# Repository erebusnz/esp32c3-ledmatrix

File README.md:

# esp32c3 Led Matrix 6x8x8
 Led Matrix 6x 60mm 8x8 dot-matrix modules drive by max7221/7219 and an esp32c3.

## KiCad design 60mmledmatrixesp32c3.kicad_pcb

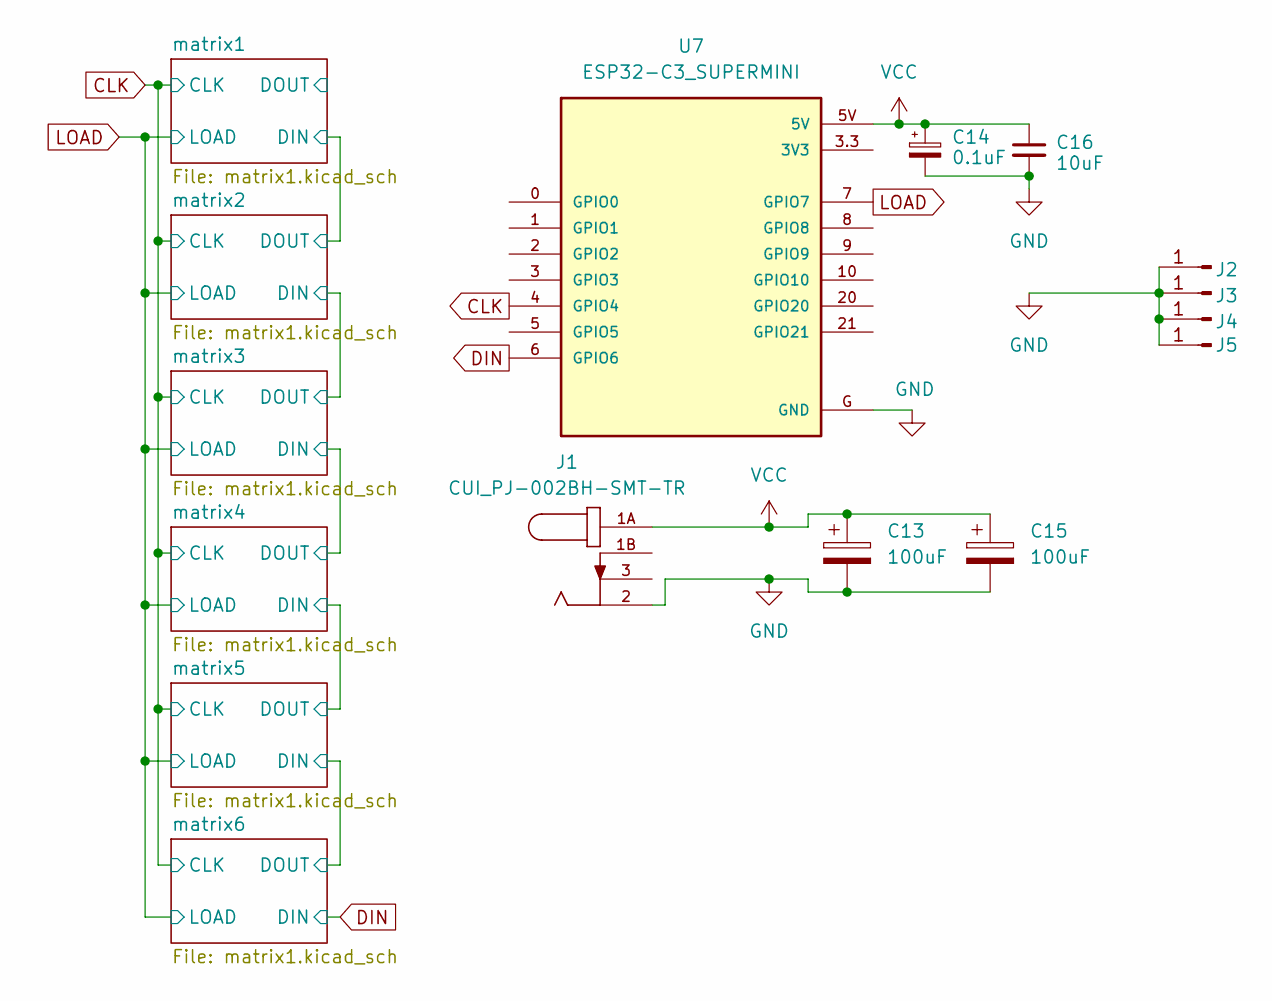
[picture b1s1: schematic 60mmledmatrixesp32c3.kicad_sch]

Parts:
C13, C15: 100uF; CAP_16SVPC100M; MPN 16SVPC100M
C14: 0.1uF; C_1206_3216Metric
C16: 10uF; C_1206_3216Metric
J1: CUI_PJ-002BH-SMT-TR; PARTREV C
J2, J3, J4, J5: Grounded Mounting Hole; MountingHole_3.2mm_M3_Pad_TopBottom
U7: ESP32-C3_SUPERMINI; MODULE_ESP32-C3_SUPERMINI

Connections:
CLK: U7.4 (GPIO4); also elsewhere on the board
DIN: U7.6 (GPIO6); also elsewhere on the board
GND: C13.2, C14.2, C15.2, C16.2, J1.2, J2.1, J3.1, J4.1, J5.1, U7.G (GND); also elsewhere on the board
LOAD: U7.7 (GPIO7); also elsewhere on the board
VCC: C13.1, C14.1, C15.1, C16.1, J1.1A, U7.5V; also elsewhere on the board

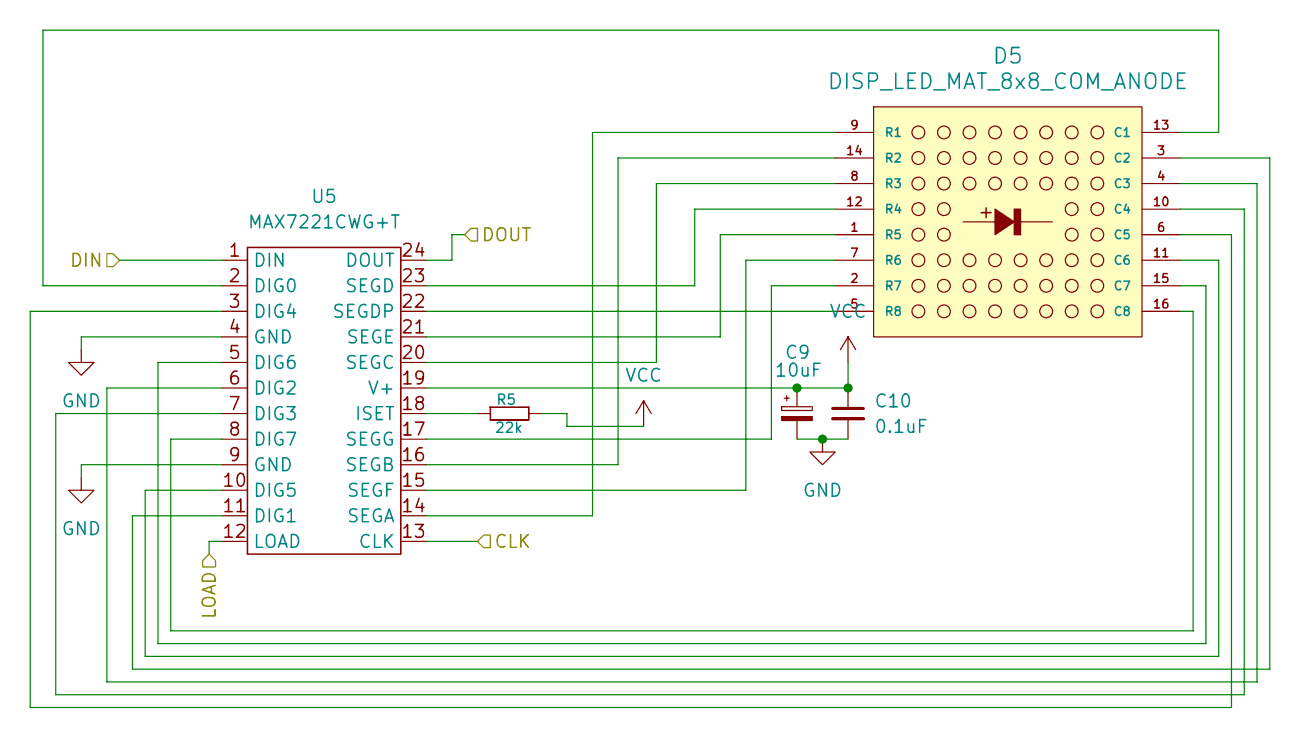
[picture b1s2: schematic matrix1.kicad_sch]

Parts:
C9: 10uF; C_1206_3216Metric
C10: 0.1uF; C_1206_3216Metric
D5: DISP_LED_MAT_8x8_COM_ANODE; LED_8x8_5MM_60x60MM
R5: 22k; R_1206_3216Metric
U5: MAX7221CWG+T; MAX7221CWG

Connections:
/matrix4/DIN: U5.24 (DOUT); also elsewhere on the board
/matrix5/DIN: U5.1 (DIN); also elsewhere on the board
CLK: U5.13 (CLK); also elsewhere on the board
GND: C9.2, C10.2, U5.4 (GND), U5.9 (GND); also elsewhere on the board
LOAD: U5.12 (LOAD); also elsewhere on the board
unnamed: D5.13 (C1), U5.2 (DIG0)
unnamed: D5.3 (C2), U5.11 (DIG1)
unnamed: D5.4 (C3), U5.6 (DIG2)
unnamed: D5.10 (C4), U5.7 (DIG3)
unnamed: D5.6 (C5), U5.3 (DIG4)
unnamed: D5.11 (C6), U5.10 (DIG5)
unnamed: D5.15 (C7), U5.5 (DIG6)
unnamed: D5.16 (C8), U5.8 (DIG7)
unnamed: D5.9 (R1), U5.14 (SEGA)
unnamed: D5.14 (R2), U5.16 (SEGB)
unnamed: D5.8 (R3), U5.20 (SEGC)
unnamed: D5.12 (R4), U5.23 (SEGD)
unnamed: D5.1 (R5), U5.21 (SEGE)
unnamed: D5.7 (R6), U5.15 (SEGF)
unnamed: D5.2 (R7), U5.17 (SEGG)
unnamed: D5.5 (R8), U5.22 (SEGDP)
unnamed: R5.1, U5.18 (ISET)
VCC: C9.1, C10.1, R5.2, U5.19 (V+); also elsewhere on the board

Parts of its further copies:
C1, C3, C5, C7, C11: 10uF; C_1206_3216Metric
C2, C4, C6, C8, C12: 0.1uF; C_1206_3216Metric
D1, D2, D3, D4, D6: DISP_LED_MAT_8x8_COM_ANODE; LED_8x8_5MM_60x60MM
R1, R2, R3, R4, R6: 22k; R_1206_3216Metric
U1, U2, U3, U4, U6: MAX7221CWG+T; MAX7221CWG

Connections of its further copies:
/matrix1/DIN: U1.1 (DIN), U2.24 (DOUT)
/matrix1/DOUT: U1.24 (DOUT)
/matrix2/DIN: U2.1 (DIN), U3.24 (DOUT)
/matrix3/DIN: U3.1 (DIN), U4.24 (DOUT)
/matrix4/DIN: U4.1 (DIN); also elsewhere on the board
/matrix5/DIN: U6.24 (DOUT); also elsewhere on the board
CLK: U1.13 (CLK), U2.13 (CLK), U3.13 (CLK), U4.13 (CLK), U6.13 (CLK); also elsewhere on the board
DIN: U6.1 (DIN); also elsewhere on the board
GND: C1.2, C2.2, C3.2, C4.2, C5.2, C6.2, C7.2, C8.2, C11.2, C12.2, U1.4 (GND), U1.9 (GND), U2.4 (GND), U2.9 (GND), U3.4 (GND), U3.9 (GND), U4.4 (GND), U4.9 (GND), U6.4 (GND), U6.9 (GND); also elsewhere on the board
LOAD: U1.12 (LOAD), U2.12 (LOAD), U3.12 (LOAD), U4.12 (LOAD), U6.12 (LOAD); also elsewhere on the board
unnamed: D1.13 (C1), U1.2 (DIG0)
unnamed: D1.3 (C2), U1.11 (DIG1)
unnamed: D1.4 (C3), U1.6 (DIG2)
unnamed: D1.10 (C4), U1.7 (DIG3)
unnamed: D1.6 (C5), U1.3 (DIG4)
unnamed: D1.11 (C6), U1.10 (DIG5)
unnamed: D1.15 (C7), U1.5 (DIG6)
unnamed: D1.16 (C8), U1.8 (DIG7)
unnamed: D1.9 (R1), U1.14 (SEGA)
unnamed: D1.14 (R2), U1.16 (SEGB)
unnamed: D1.8 (R3), U1.20 (SEGC)
unnamed: D1.12 (R4), U1.23 (SEGD)
unnamed: D1.1 (R5), U1.21 (SEGE)
unnamed: D1.7 (R6), U1.15 (SEGF)
unnamed: D1.2 (R7), U1.17 (SEGG)
unnamed: D1.5 (R8), U1.22 (SEGDP)
unnamed: D2.13 (C1), U2.2 (DIG0)
unnamed: D2.3 (C2), U2.11 (DIG1)
unnamed: D2.4 (C3), U2.6 (DIG2)
unnamed: D2.10 (C4), U2.7 (DIG3)
unnamed: D2.6 (C5), U2.3 (DIG4)
unnamed: D2.11 (C6), U2.10 (DIG5)
unnamed: D2.15 (C7), U2.5 (DIG6)
unnamed: D2.16 (C8), U2.8 (DIG7)
unnamed: D2.9 (R1), U2.14 (SEGA)
unnamed: D2.14 (R2), U2.16 (SEGB)
unnamed: D2.8 (R3), U2.20 (SEGC)
unnamed: D2.12 (R4), U2.23 (SEGD)
unnamed: D2.1 (R5), U2.21 (SEGE)
unnamed: D2.7 (R6), U2.15 (SEGF)
unnamed: D2.2 (R7), U2.17 (SEGG)
unnamed: D2.5 (R8), U2.22 (SEGDP)
unnamed: D3.13 (C1), U3.2 (DIG0)
unnamed: D3.3 (C2), U3.11 (DIG1)
unnamed: D3.4 (C3), U3.6 (DIG2)
unnamed: D3.10 (C4), U3.7 (DIG3)
unnamed: D3.6 (C5), U3.3 (DIG4)
unnamed: D3.11 (C6), U3.10 (DIG5)
unnamed: D3.15 (C7), U3.5 (DIG6)
unnamed: D3.16 (C8), U3.8 (DIG7)
unnamed: D3.9 (R1), U3.14 (SEGA)
unnamed: D3.14 (R2), U3.16 (SEGB)
unnamed: D3.8 (R3), U3.20 (SEGC)
unnamed: D3.12 (R4), U3.23 (SEGD)
unnamed: D3.1 (R5), U3.21 (SEGE)
unnamed: D3.7 (R6), U3.15 (SEGF)
unnamed: D3.2 (R7), U3.17 (SEGG)
unnamed: D3.5 (R8), U3.22 (SEGDP)
unnamed: D4.13 (C1), U4.2 (DIG0)
unnamed: D4.3 (C2), U4.11 (DIG1)
unnamed: D4.4 (C3), U4.6 (DIG2)
unnamed: D4.10 (C4), U4.7 (DIG3)
unnamed: D4.6 (C5), U4.3 (DIG4)
unnamed: D4.11 (C6), U4.10 (DIG5)
unnamed: D4.15 (C7), U4.5 (DIG6)
unnamed: D4.16 (C8), U4.8 (DIG7)
unnamed: D4.9 (R1), U4.14 (SEGA)
unnamed: D4.14 (R2), U4.16 (SEGB)
unnamed: D4.8 (R3), U4.20 (SEGC)
unnamed: D4.12 (R4), U4.23 (SEGD)
unnamed: D4.1 (R5), U4.21 (SEGE)
unnamed: D4.7 (R6), U4.15 (SEGF)
unnamed: D4.2 (R7), U4.17 (SEGG)
unnamed: D4.5 (R8), U4.22 (SEGDP)
unnamed: D6.13 (C1), U6.2 (DIG0)
unnamed: D6.3 (C2), U6.11 (DIG1)
unnamed: D6.4 (C3), U6.6 (DIG2)
unnamed: D6.10 (C4), U6.7 (DIG3)
unnamed: D6.6 (C5), U6.3 (DIG4)
unnamed: D6.11 (C6), U6.10 (DIG5)
unnamed: D6.15 (C7), U6.5 (DIG6)
unnamed: D6.16 (C8), U6.8 (DIG7)
unnamed: D6.9 (R1), U6.14 (SEGA)
unnamed: D6.14 (R2), U6.16 (SEGB)
unnamed: D6.8 (R3), U6.20 (SEGC)
unnamed: D6.12 (R4), U6.23 (SEGD)
unnamed: D6.1 (R5), U6.21 (SEGE)
unnamed: D6.7 (R6), U6.15 (SEGF)
unnamed: D6.2 (R7), U6.17 (SEGG)
unnamed: D6.5 (R8), U6.22 (SEGDP)
unnamed: R1.1, U1.18 (ISET)
unnamed: R2.1, U2.18 (ISET)
unnamed: R3.1, U3.18 (ISET)
unnamed: R4.1, U4.18 (ISET)
unnamed: R6.1, U6.18 (ISET)
VCC: C1.1, C2.1, C3.1, C4.1, C5.1, C6.1, C7.1, C8.1, C11.1, C12.1, R1.2, R2.2, R3.2, R4.2, R6.2, U1.19 (V+), U2.19 (V+), U3.19 (V+), U4.19 (V+), U6.19 (V+); also elsewhere on the board

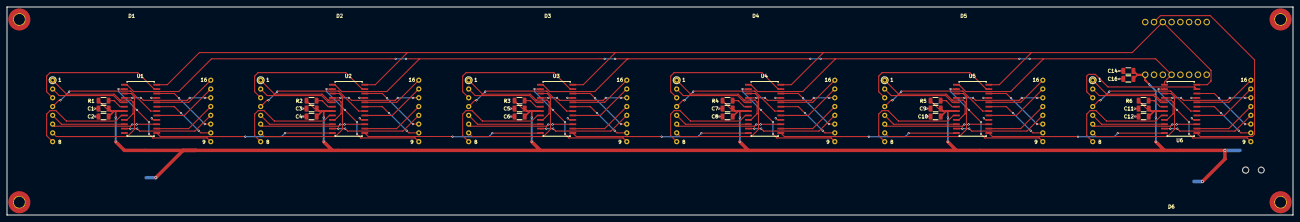
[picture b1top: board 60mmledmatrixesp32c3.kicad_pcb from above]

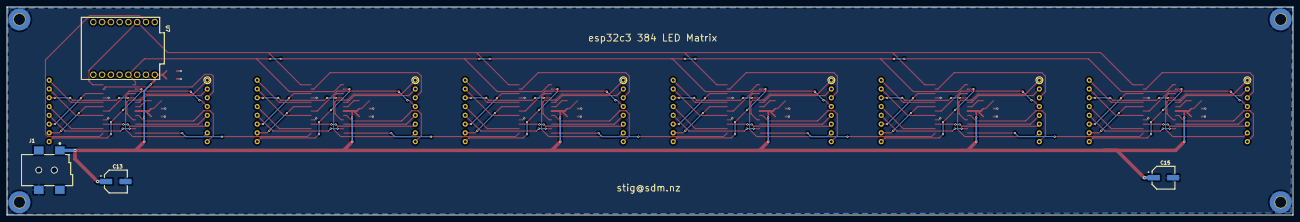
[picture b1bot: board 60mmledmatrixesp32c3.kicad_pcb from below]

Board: 2 copper layers, 372.2 x 60.2 mm, 40 parts (4 on the bottom side), 112 nets.

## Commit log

2024-08-17 Added project
2024-08-17 Added PDF schema
